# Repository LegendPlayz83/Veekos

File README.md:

# Veekos

Veekos is a 21-key wireless Bluetooth Macropad that uses the XIAO nRF52840 Sense as its microcontroller chip. Each key has its own diode assigned; the diodes are 1N4148.<br>

<h3>About the project</h3>
It has 21 keys, and its connectivity is through Bluetooth. <br>
In the design, you may see that there is no sign of the battery. This is because the Xiao already has an SMD space for connecting the battery, so I do not need to connect it to any pins.  <br>
 <br>

<h3>Why I made this</h3>
I have made many small macro pads consisting of 4-6keys, but this time, I wanted to go big with 21 keys. Also, this one is going to be connected via Bluetooth, giving me a huge relief from wired macro pads. 

<h3>Challenges faced</h3>
Although there were no major problems or challenges, while making its case, I had to change the measurement of the top part twice to make it match the bottom part. <br>
Also, I had to put the 3d model for each key manually in the KiCad PCB editor, along with removing the silkscreen of each key. This was a tedious task, but I did it :)

<h2>Schematic</h2>

<h2>PCB(without silkscreen art)</h2>

<h2>PCB(with silkscreen art)</h2>

<h2>PCB(3D view)</h2>

<h2>BOM</h2>

| Name | Quantity | Cost | Link |
| :--- | :---: | :---: | :--- |
| XIAO nrf52840 sense | 1 | $24.05 | [Robu.in](https://robu.in/product/seeed-studio-xiao-nrf52840-sense-tinyml-tensorflow-lite-imu-microphone-bluetooth5-0/) |
| PCB (from JLCPCB) | 1 | $20.45 | [JLCPCB](https://jlcpcb.com/) |
| 1N4148 Diodes | 21 | $2.00 (Self-funded) | [Amazon](https://amzn.in/d/07wEWb6X) |
| 3.7V LiPo Battery | 1 | $3.06 | [Amazon](https://amzn.in/d/050THvbC) |
| TP4056 Charger Module | 1 | $1.20 | [Amazon](https://amzn.in/d/01OvmiZk) |
| DSA Keycaps gradient | 1 | $6.40 | [Curiosity Caps](https://curiositycaps.in/products/21-keys-numpad-thick-pbt-cherry-pbt-keycaps) |
| Cherry MX Keys | 21 | $6.30 | [StacksKB](https://stackskb.com/store/click-inc-of-linear-switch-pack-of-10/) |
| Stainless steel screws | 4 | $2.00 (Self-funded) | [StacksKB](https://stackskb.com/store/m2-screw-8mm-stainless-steel/) |
| 2u Stabilizers | 3 | $3.45 | [StacksKB](https://stackskb.com/store/genuine-cherry-mx-plate-mount-stabilizers-2u/) |
| Shipping | 1 | $2.00 | [StacksKB](https://stackskb.com) |
| **Total** | — | **$68.91** | — |
| **Total funding required** | — | **$64.91** | — |
## Total Pricing
The total price comes out to be 6043 INR ($63) [ SHIPPING INCLUDED ]

The pricing might slightly vary due to flash sales, and dollar market trends.

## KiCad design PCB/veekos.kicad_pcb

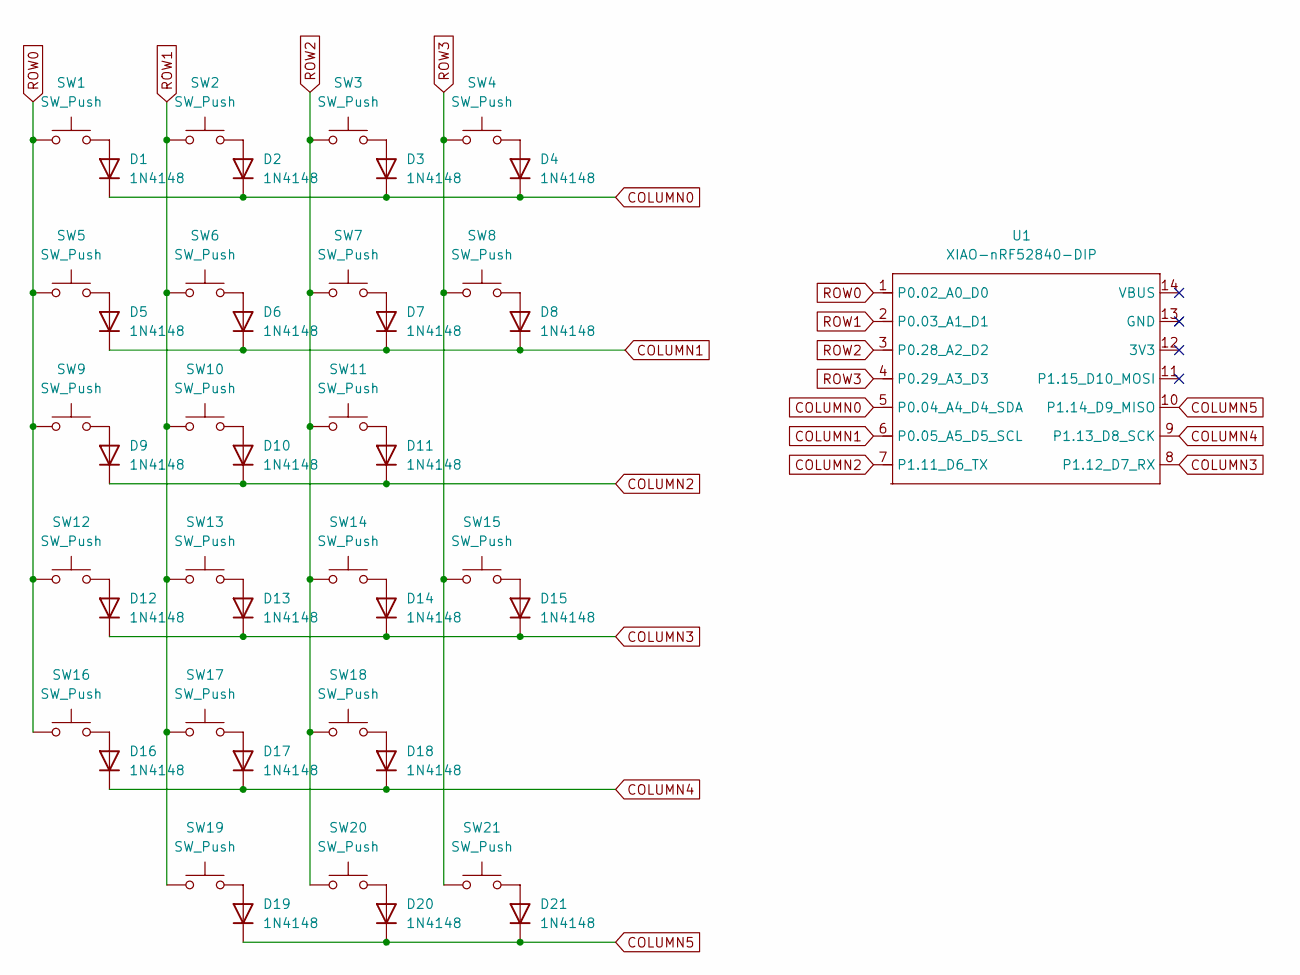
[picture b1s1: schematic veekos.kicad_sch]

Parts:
D1, D2, D3, D4, D5, D6, D7, D8, D9, D10, D11, D12, D13, D14, D15, D16, D17, D18, D19, D20, D21: 1N4148; D_DO-35_SOD27_P7.62mm_Horizontal
SW1, SW2, SW3, SW4, SW5, SW6, SW7, SW8, SW9, SW10, SW11, SW12, SW13, SW14, SW16, SW17, SW18, SW21: SW_Push; SW_Cherry_MX_1.00u_PCB
SW15, SW19: SW_Push; SW_Cherry_MX_2.00u_Vertical_PCB
SW20: SW_Push; SW_Cherry_MX_2.00u_PCB
U1: XIAO-nRF52840-DIP

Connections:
COLUMN0: D1.1 (K), D2.1 (K), D3.1 (K), D4.1 (K), U1.5 (P0.04_A4_D4_SDA)
COLUMN1: D5.1 (K), D6.1 (K), D7.1 (K), D8.1 (K), U1.6 (P0.05_A5_D5_SCL)
COLUMN2: D9.1 (K), D10.1 (K), D11.1 (K), U1.7 (P1.11_D6_TX)
COLUMN3: D12.1 (K), D13.1 (K), D14.1 (K), D15.1 (K), U1.8 (P1.12_D7_RX)
COLUMN4: D16.1 (K), D17.1 (K), D18.1 (K), U1.9 (P1.13_D8_SCK)
COLUMN5: D19.1 (K), D20.1 (K), D21.1 (K), U1.10 (P1.14_D9_MISO)
unnamed: D1.2 (A), SW1.2
unnamed: D2.2 (A), SW2.2
unnamed: D3.2 (A), SW3.2
unnamed: D4.2 (A), SW4.2
unnamed: D5.2 (A), SW5.2
unnamed: D6.2 (A), SW6.2
unnamed: D7.2 (A), SW7.2
unnamed: D8.2 (A), SW8.2
unnamed: D9.2 (A), SW9.2
unnamed: D10.2 (A), SW10.2
unnamed: D11.2 (A), SW11.2
unnamed: D12.2 (A), SW12.2
unnamed: D13.2 (A), SW13.2
unnamed: D14.2 (A), SW14.2
unnamed: D15.2 (A), SW15.2
unnamed: D16.2 (A), SW16.2
unnamed: D17.2 (A), SW17.2
unnamed: D18.2 (A), SW18.2
unnamed: D19.2 (A), SW19.2
unnamed: D20.2 (A), SW20.2
unnamed: D21.2 (A), SW21.2
ROW0: SW1.1, SW5.1, SW9.1, SW12.1, SW16.1, U1.1 (P0.02_A0_D0)
ROW1: SW2.1, SW6.1, SW10.1, SW13.1, SW17.1, SW19.1, U1.2 (P0.03_A1_D1)
ROW2: SW3.1, SW7.1, SW11.1, SW14.1, SW18.1, SW20.1, U1.3 (P0.28_A2_D2)
ROW3: SW4.1, SW8.1, SW15.1, SW21.1, U1.4 (P0.29_A3_D3)

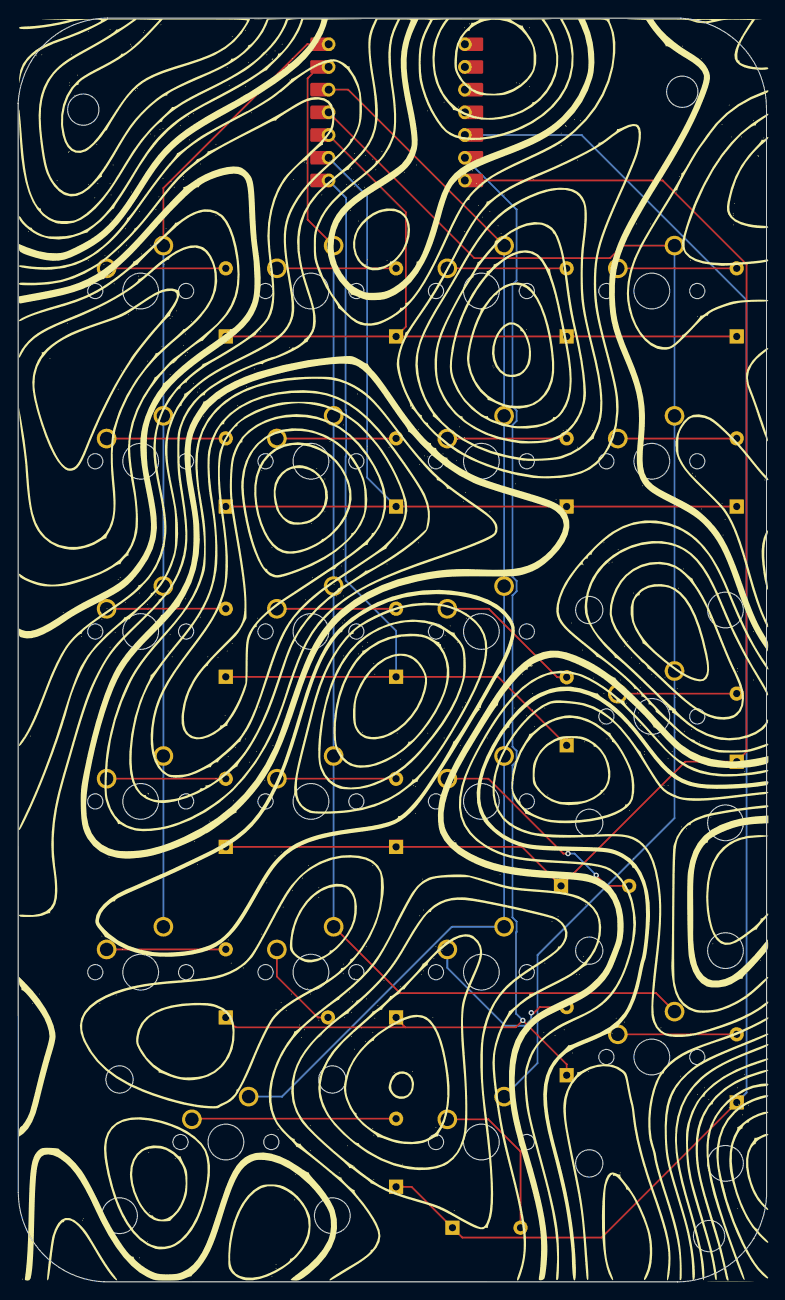
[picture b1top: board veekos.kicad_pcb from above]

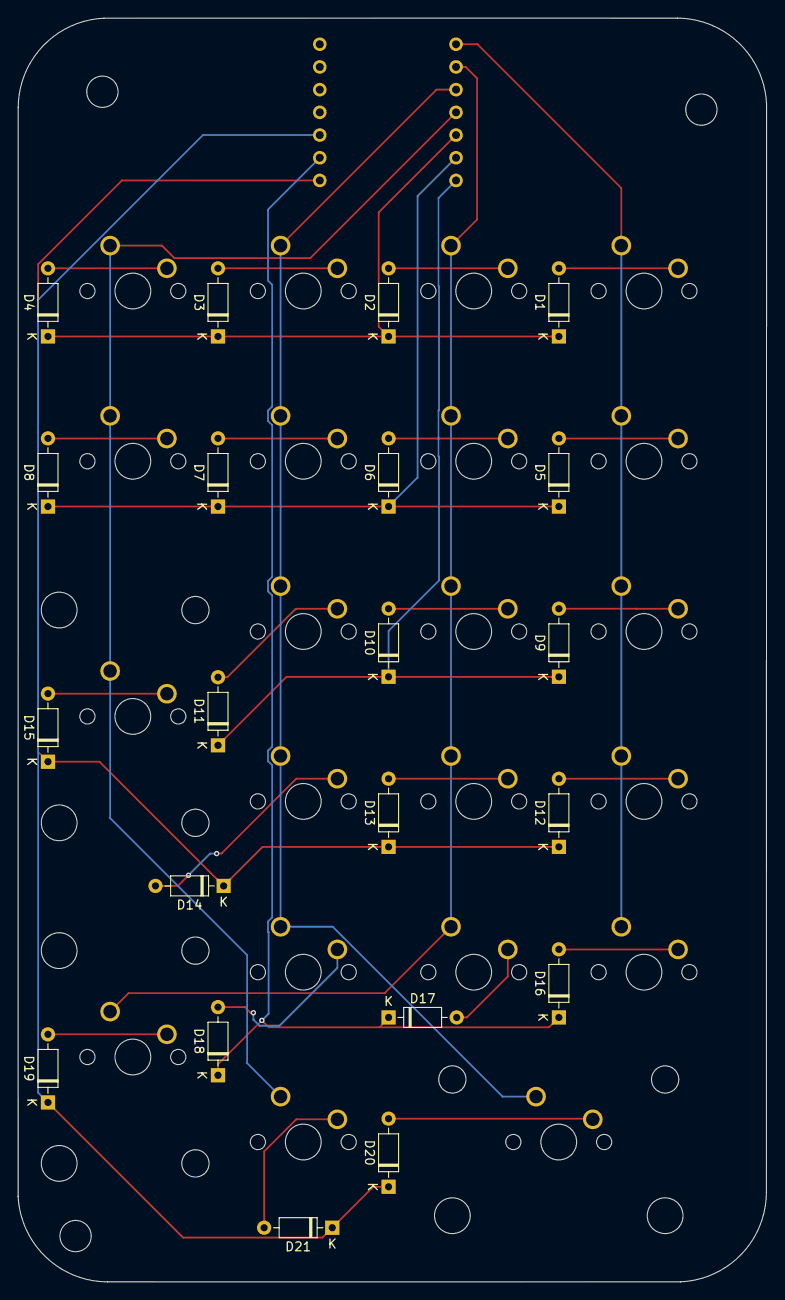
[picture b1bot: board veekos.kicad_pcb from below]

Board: 2 copper layers, 83.7 x 141.4 mm, 43 parts (21 on the bottom side), 31 nets.
